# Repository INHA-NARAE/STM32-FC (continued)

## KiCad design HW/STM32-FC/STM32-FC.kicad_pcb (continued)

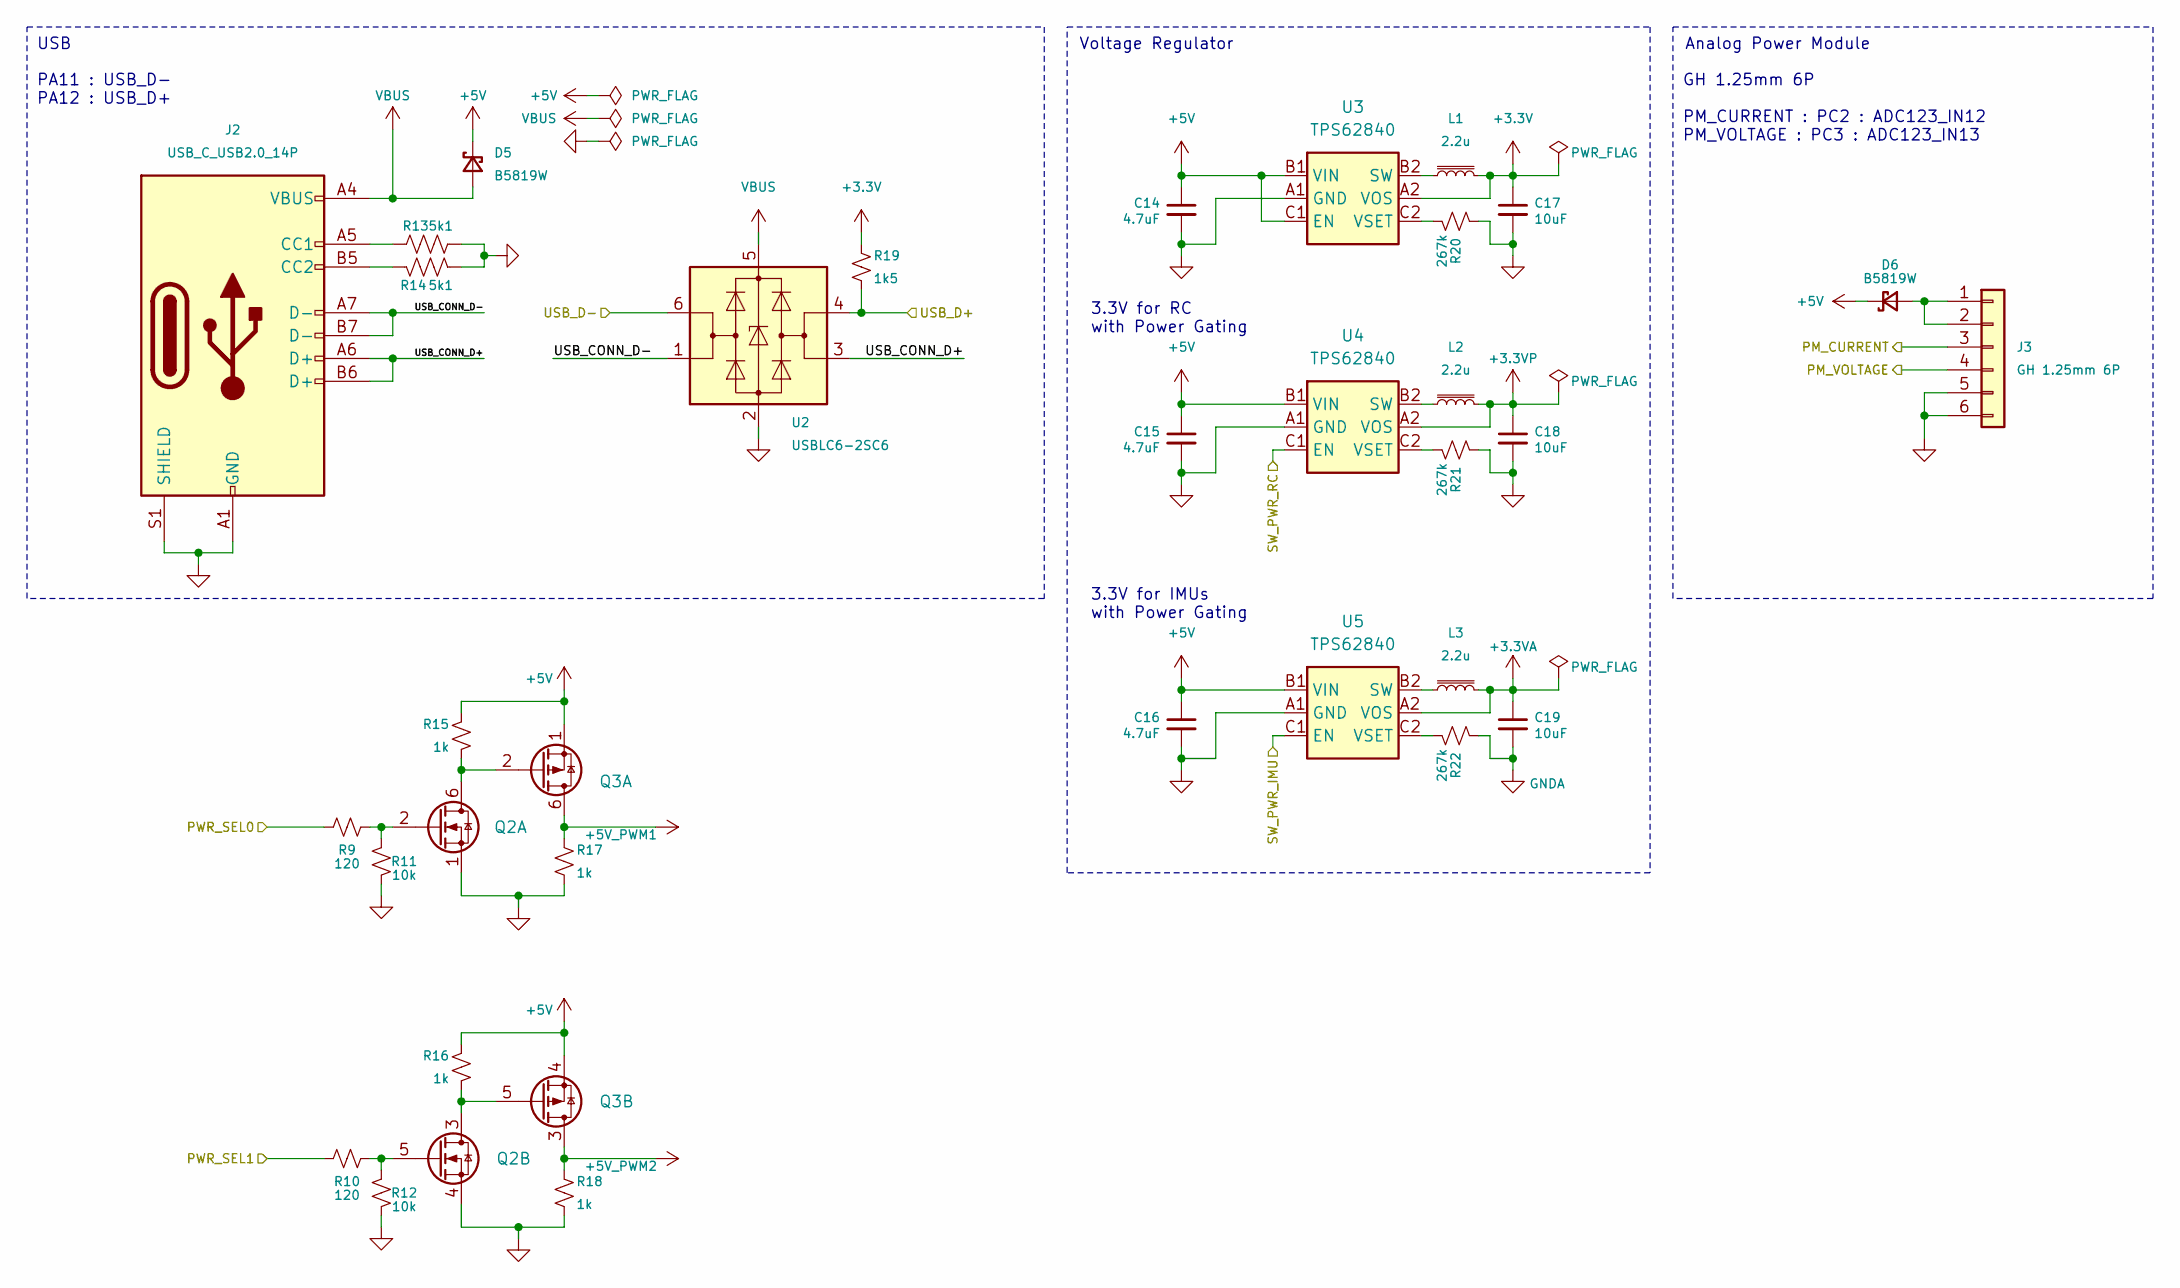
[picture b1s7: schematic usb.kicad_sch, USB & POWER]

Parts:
C14, C15, C16: 4.7uF; C_0402_1005Metric; LCSC C307423
C17, C18, C19: 10uF; C_0402_1005Metric; LCSC C307415
D5, D6: B5819W; D_SOD-323; LCSC C22624
J2: USB_C_USB2.0_14P; USB_C_Receptacle_GCT_USB4110; LCSC C709031
J3: GH 1.25mm 6P; JST_GH_SM06B-GHS-TB_06x1.25mm_Angled; LCSC C133065
L1, L2, L3: 2.2u; VLS201610ET-2R2M; LCSC C114768
Q2: PMDPB30XN; Nexperia_SOT1118; LCSC C478009
Q3: PMDPB55XP; Nexperia_SOT1118; LCSC C552752
R9, R10: 120; R_0402_1005Metric; LCSC C25079
R11, R12: 10k; R_0402_1005Metric; LCSC C25531
R13, R14: 5k1; R_0402_1005Metric; LCSC C25905
R15, R16, R17, R18: 1k; R_0402_1005Metric; LCSC C106235
R19: 1k5; R_0402_1005Metric; LCSC C25867
R20, R21, R22: 267k; R_0402_1005Metric; LCSC C2998050
U2: USBLC6-2SC6; SOT-23-6; LCSC C7519
U3, U4, U5: TPS62840; Texas_DSBGA-6_0.855x1.255mm_Layout2x3_P0.4mm_LevelC; LCSC C2071139

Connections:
+3.3V: C17.1, L1.2, R19.1, U3.A2 (VOS); also elsewhere on the board
+3.3VA: C19.1, L3.2, U5.A2 (VOS); also elsewhere on the board
+3.3VP: C18.1, L2.2, U4.A2 (VOS); also elsewhere on the board
+5V: C14.1, C15.1, C16.1, D5.1 (K), D6.1 (K), Q3.1 (S), Q3.4 (S), R15.1, R16.1, U3.B1 (VIN), U3.C1 (EN), U4.B1 (VIN), U5.B1 (VIN); also elsewhere on the board
+5V_PWM1: Q3.6 (D), Q3.7 (D), R17.1; also elsewhere on the board
+5V_PWM2: Q3.3 (D), Q3.8 (D), R18.1; also elsewhere on the board
/PM_CURRENT: J3.3; also elsewhere on the board
/PM_VOLTAGE: J3.4; also elsewhere on the board
/PWR_SEL0: R9.1; also elsewhere on the board
/PWR_SEL1: R10.1; also elsewhere on the board
/SW_PWR_IMU: U5.C1 (EN); also elsewhere on the board
/SW_PWR_RC: U4.C1 (EN); also elsewhere on the board
/USB & POWER/USB_CONN_D+: J2.A6 (D+), J2.B6 (D+), U2.3 (I/O2)
/USB & POWER/USB_CONN_D-: J2.A7 (D-), J2.B7 (D-), U2.1 (I/O1)
/USB_D+: R19.2, U2.4 (I/O2); also elsewhere on the board
/USB_D-: U2.6 (I/O1); also elsewhere on the board
unnamed: D6.2 (A), J3.1, J3.2
unnamed: J2.A5 (CC1), R13.1
unnamed: J2.B5 (CC2), R14.1
unnamed: Q2.2 (G), R9.2, R11.1
unnamed: Q2.5 (G), R10.2, R12.1
unnamed: Q2.6 (D), Q2.7 (D), Q3.2 (G), R15.2
unnamed: Q2.3 (D), Q2.8 (D), Q3.5 (G), R16.2
unnamed: L1.1, U3.B2 (SW)
unnamed: R20.2, U3.C2 (VSET)
unnamed: L2.1, U4.B2 (SW)
unnamed: R21.2, U4.C2 (VSET)
unnamed: L3.1, U5.B2 (SW)
unnamed: R22.2, U5.C2 (VSET)
VBUS: D5.2 (A), J2.A4 (VBUS), J2.A9 (VBUS), J2.B4 (VBUS), J2.B9 (VBUS), U2.5 (VBUS)

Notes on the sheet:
Analog Power Module
GH 1.25mm 6P PM_CURRENT : PC2 : ADC123_IN12 PM_VOLTAGE : PC3 : ADC123_IN13
Voltage Regulator
3.3V for IMUs with Power Gating
USB
3.3V for RC with Power Gating
PA11 : USB_D- PA12 : USB_D+

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
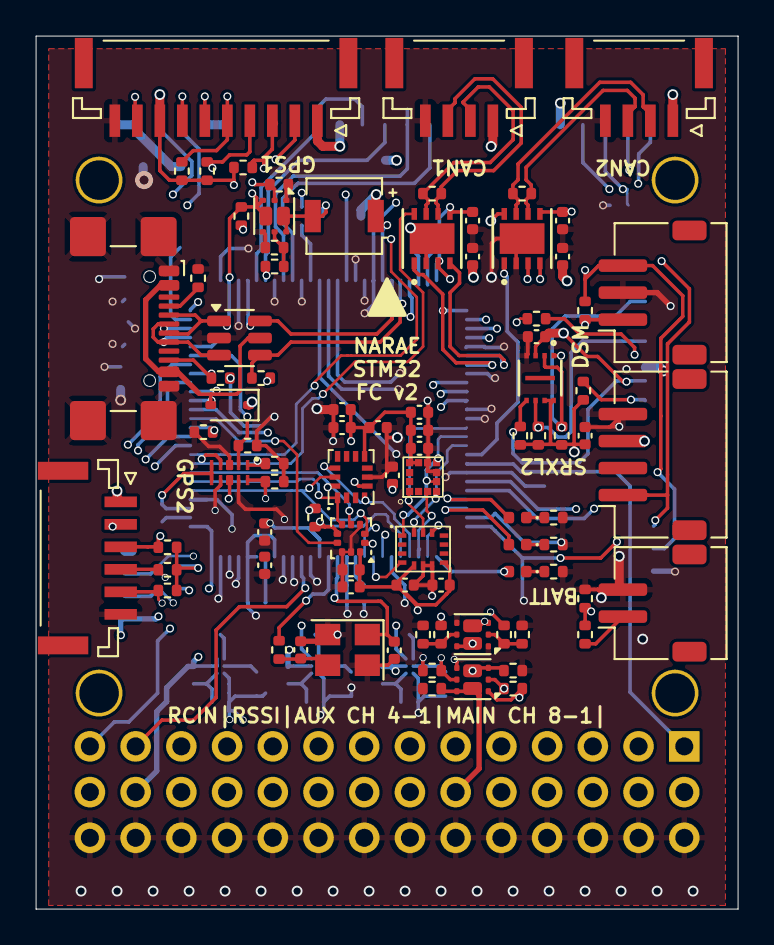
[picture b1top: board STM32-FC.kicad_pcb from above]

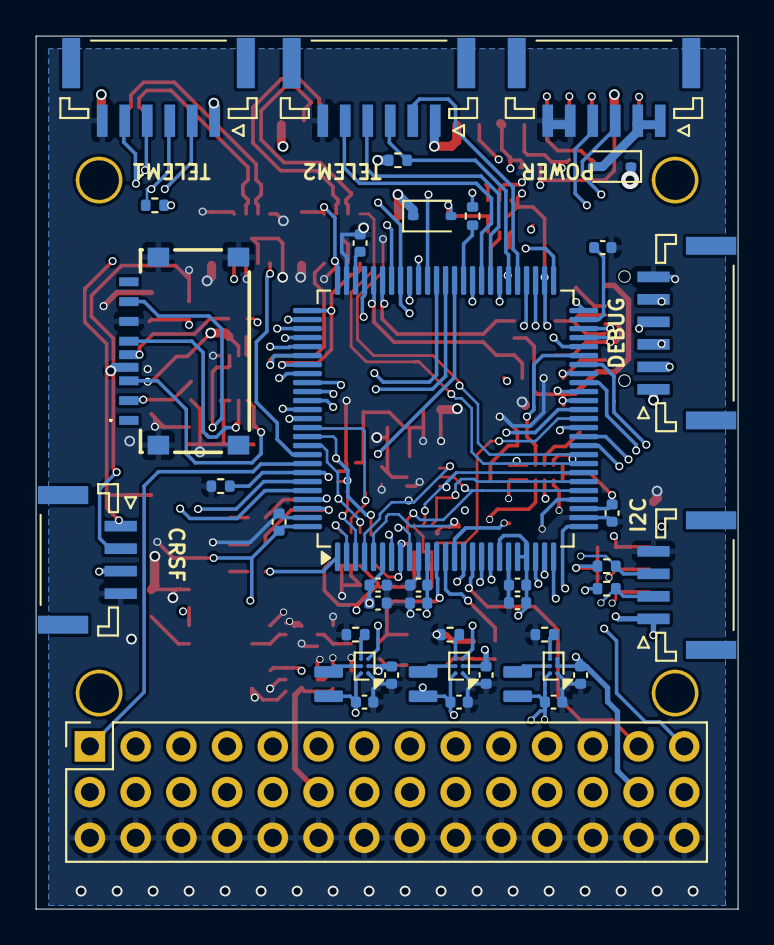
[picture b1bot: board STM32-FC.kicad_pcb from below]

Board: 4 copper layers, 39.0 x 48.5 mm, 133 parts (42 on the bottom side), 125 nets.

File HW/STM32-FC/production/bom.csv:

Designator,Footprint,Quantity,Value,LCSC Part #
BZ1,FUET-4020,1,FUET-4020,C391027
"C1, C4",0402,2,10pF,C1545
"C10, C11, C13, C20, C21, C22, C24, C29, C3, C30, C32, C33, C34, C35, C5, C8, C9",0402,17,100nF,C1525
C12,0402,1,1uF,C14445
"C14, C15, C16, C27",0402,4,4.7uF,C307423
"C17, C18, C19, C2, C28",0402,5,10uF,C307415
C23,0402,1,100pF,C152819
C25,0402,1,2.2nF,C84703
C26,0402,1,10nF,C15195
C31,0402,1,220nF,C16651
"C6, C7",0402,2,2.2uF,C170151
"D1, D5, D6",D_SOD-323,3,B5819W,C22624
D2,0402,1,Red,C130719
D3,0402,1,Yellow,C130721
D4,0402,1,Green,C130722
"J1, J10, J11, J12, J3",JST_GH_SM06B-GHS-TB_06x1.25mm_Angled,5,GH 1.25mm 6P,C133065
"J13, J14, J15, J16",JST_GH_SM04B-GHS-TB_04x1.25mm_Angled,4,GH 1.25mm 4P,C189895
J2,USB_C_Receptacle_GCT_USB4110,1,USB_C_USB2.0_14P,C709031
J4,TF06A,1,TF-06A,C693844
J5,JST_ZH_S2B-ZR-SM4A-TF_1x02-1MP_P1.50mm_Horizontal,1,JST ZH 1.5mm 2P,C265329
J6,PWM_Conn_3x14,1,PWM_Conn_3x14,C3327492
J7,JST_ZH_S4B-ZR-SM4A-TF_1x04-1MP_P1.50mm_Horizontal,1,ZH 1.5mm 4P,C485354
J8,JST_ZH_S3B-ZR-SM4A-TF_1x03-1MP_P1.50mm_Horizontal,1,ZH 1.5mm 3P,C72591
J9,JST_GH_SM10B-GHS-TB_10x1.25mm_Angled,1,GH 1.25mm 10P,C2683602 
"L1, L2, L3",VLS201610ET-2R2M,3,2.2u,C114768
"Q1, Q2",Nexperia_SOT1118,2,PMDPB30XN,C478009
Q3,Nexperia_SOT1118,1,PMDPB55XP,C552752
"R1, R11, R12, R2, R23, R24, R25, R26, R27, R28, R31, R32, R34, R36, R37, R38, R39, R40, R41, R42, R43, R44, R45, R46, R47, R5",0402,26,10k,C25531
"R10, R3, R33, R4, R48, R49, R6, R7, R8, R9",0402,10,120, C25079
"R13, R14",0402,2,5k1,C25905
"R15, R16, R17, R18, R30, R35",0402,6,1k,C106235
R19,0402,1,1k5,C25867
"R20, R21, R22",0402,3,267k,C2998050
R29,0402,1,15k,C25539
U1,LQFP-100_14x14mm_P0.5mm,1,STM32F407VETx,C28730
U10,ST_HLGA-10_2x2mm_P0.5mm_LayoutBorder3x2y,1,LPS22HH,C2827824
U11,TMUX1104,1,TMUX1104,C2865387
"U12, U13",VDFN8_3X3_MCH-L,2,ATA6561-GBQW,C617297
U2,SOT-23-6,1,USBLC6-2SC6,C7519
"U3, U4, U5",Texas_DSBGA-6_0.855x1.255mm_Layout2x3_P0.4mm_LevelC,3,TPS62840,C2071139
U6,USON_LUXIG TR_WIN-L,1,W25X40CLUXIG,C401661
U7,BMI323_L,1,BMI323,C5368700
U8,IIM42352_L,1,ICM-42688-P,C1850418
U9,LIS2MDLTR,1,LIS2MDLTR,C919695
Y1,Crystal_SMD_Abracon_ABM8G-4Pin_3.2x2.5mm,1,16MHz,C1985423

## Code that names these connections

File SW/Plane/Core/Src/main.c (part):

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		  FS_mannualMode();
	  }
	  else{
		  LL_GPIO_ResetOutputPin(LED_RED_GPIO_Port, LED_RED_Pin);
		  SERVO_control();
	  }

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
  LL_AHB1_GRP1_EnableClock(LL_AHB1_GRP1_PERIPH_GPIOC);
  /**ADC1 GPIO Configuration
  PC1   ------> ADC1_IN11
  */
  GPIO_InitStruct.Pin = RSSI_Pin;
  GPIO_InitStruct.Mode = LL_GPIO_MODE_ANALOG;
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
  LL_AHB1_GRP1_EnableClock(LL_AHB1_GRP1_PERIPH_GPIOA);
  /**SPI1 GPIO Configuration
  PA5   ------> SPI1_SCK
  PA6   ------> SPI1_MISO
  PA7   ------> SPI1_MOSI
  */
  GPIO_InitStruct.Pin = LL_GPIO_PIN_5|LL_GPIO_PIN_6|LL_GPIO_PIN_7;
  GPIO_InitStruct.Mode = LL_GPIO_MODE_ALTERNATE;
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  /* USER CODE END TIM1_Init 2 */
  LL_AHB1_GRP1_EnableClock(LL_AHB1_GRP1_PERIPH_GPIOE);
  /**TIM1 GPIO Configuration
  PE11   ------> TIM1_CH2
  PE13   ------> TIM1_CH3
  */
  GPIO_InitStruct.Pin = MAIN_CH11_Pin|MAIN_CH12_Pin;
  GPIO_InitStruct.Mode = LL_GPIO_MODE_ALTERNATE;
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  LL_AHB1_GRP1_EnableClock(LL_AHB1_GRP1_PERIPH_GPIOB);
  LL_AHB1_GRP1_EnableClock(LL_AHB1_GRP1_PERIPH_GPIOC);
  /**TIM3 GPIO Configuration
  PB0   ------> TIM3_CH3
  PB1   ------> TIM3_CH4
  PC6   ------> TIM3_CH1
  PC7   ------> TIM3_CH2
  */
  GPIO_InitStruct.Pin = MAIN_CH9_Pin|MAIN_CH10_Pin;
  GPIO_InitStruct.Mode = LL_GPIO_MODE_ALTERNATE;
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  LL_AHB1_GRP1_EnableClock(LL_AHB1_GRP1_PERIPH_GPIOD);
  LL_AHB1_GRP1_EnableClock(LL_AHB1_GRP1_PERIPH_GPIOB);
  /**TIM4 GPIO Configuration
  PD14   ------> TIM4_CH3
  PD15   ------> TIM4_CH4
  PB7   ------> TIM4_CH2
  */
  GPIO_InitStruct.Pin = Buzzer_Pin|MAIN_CH4_Pin;
  GPIO_InitStruct.Mode = LL_GPIO_MODE_ALTERNATE;
  GPIO_InitStruct.Speed = LL_GPIO_SPEED_FREQ_LOW;
  GPIO_InitStruct.OutputType = LL_GPIO_OUTPUT_PUSHPULL;
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  /* USER CODE END TIM5_Init 2 */
  LL_AHB1_GRP1_EnableClock(LL_AHB1_GRP1_PERIPH_GPIOA);
  /**TIM5 GPIO Configuration
  PA0-WKUP   ------> TIM5_CH1
  PA1   ------> TIM5_CH2
  PA2   ------> TIM5_CH3
  PA3   ------> TIM5_CH4
  */
  GPIO_InitStruct.Pin = MAIN_CH5_Pin|MAIN_CH6_Pin|MAIN_CH7_Pin|MAIN_CH8_Pin;
  GPIO_InitStruct.Mode = LL_GPIO_MODE_ALTERNATE;
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
  LL_AHB1_GRP1_EnableClock(LL_AHB1_GRP1_PERIPH_GPIOC);
  /**UART4 GPIO Configuration
  PC10   ------> UART4_TX
  PC11   ------> UART4_RX
  */
  GPIO_InitStruct.Pin = GPS1_TX_Pin|GPS2_RX_Pin;
  GPIO_InitStruct.Mode = LL_GPIO_MODE_ALTERNATE;
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  LL_AHB1_GRP1_EnableClock(LL_AHB1_GRP1_PERIPH_GPIOC);
  LL_AHB1_GRP1_EnableClock(LL_AHB1_GRP1_PERIPH_GPIOD);
  /**UART5 GPIO Configuration
  PC12   ------> UART5_TX
  PD2   ------> UART5_RX
  */
  GPIO_InitStruct.Pin = GPS2_TX_Pin;
  GPIO_InitStruct.Mode = LL_GPIO_MODE_ALTERNATE;
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
  LL_AHB1_GRP1_EnableClock(LL_AHB1_GRP1_PERIPH_GPIOA);
  /**USART1 GPIO Configuration
  PA9   ------> USART1_TX
  */
  GPIO_InitStruct.Pin = RC_SRXL2_Pin;
  GPIO_InitStruct.Mode = LL_GPIO_MODE_ALTERNATE;
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
  LL_AHB1_GRP1_EnableClock(LL_AHB1_GRP1_PERIPH_GPIOD);
  /**USART2 GPIO Configuration
  PD3   ------> USART2_CTS
  PD4   ------> USART2_RTS
  PD5   ------> USART2_TX
  PD6   ------> USART2_RX
  */
  GPIO_InitStruct.Pin = LL_GPIO_PIN_3|LL_GPIO_PIN_4|Telm1_TX_Pin|Telm1_RX_Pin;
  GPIO_InitStruct.Mode = LL_GPIO_MODE_ALTERNATE;
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
  LL_AHB1_GRP1_EnableClock(LL_AHB1_GRP1_PERIPH_GPIOD);
  /**USART3 GPIO Configuration
  PD8   ------> USART3_TX
  PD9   ------> USART3_RX
  PD11   ------> USART3_CTS
  PD12   ------> USART3_RTS
  */
  GPIO_InitStruct.Pin = Telm2_TX_Pin|Telm2_RX_Pin|LL_GPIO_PIN_11|LL_GPIO_PIN_12;
  GPIO_InitStruct.Mode = LL_GPIO_MODE_ALTERNATE;
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  LL_AHB1_GRP1_EnableClock(LL_AHB1_GRP1_PERIPH_GPIOD);

  /**/
  LL_GPIO_ResetOutputPin(GPIOE, LED_BLUE_Pin|GYRO1_NSS_Pin|BARO_NSS_Pin|LED_RED_Pin
                          |LED_YELLOW_Pin);

  /**/
  LL_GPIO_ResetOutputPin(GPS1_SW_LED_GPIO_Port, GPS1_SW_LED_Pin);

  /**/
  GPIO_InitStruct.Pin = LED_BLUE_Pin|GYRO1_NSS_Pin|BARO_NSS_Pin|LED_RED_Pin
                          |LED_YELLOW_Pin;
  GPIO_InitStruct.Mode = LL_GPIO_MODE_OUTPUT;
  GPIO_InitStruct.Speed = LL_GPIO_SPEED_FREQ_LOW;
  GPIO_InitStruct.OutputType = LL_GPIO_OUTPUT_PUSHPULL;
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  LL_GPIO_Init(GPIOE, &GPIO_InitStruct);

  /**/
  GPIO_InitStruct.Pin = BARO_INT_Pin;
  GPIO_InitStruct.Mode = LL_GPIO_MODE_INPUT;
  GPIO_InitStruct.Pull = LL_GPIO_PULL_NO;
  LL_GPIO_Init(BARO_INT_GPIO_Port, &GPIO_InitStruct);

  /**/
  GPIO_InitStruct.Pin = GPS1_SW_LED_Pin;
  GPIO_InitStruct.Mode = LL_GPIO_MODE_OUTPUT;
  GPIO_InitStruct.Speed = LL_GPIO_SPEED_FREQ_LOW;
  GPIO_InitStruct.OutputType = LL_GPIO_OUTPUT_PUSHPULL;
  GPIO_InitStruct.Pull = LL_GPIO_PULL_NO;
  LL_GPIO_Init(GPS1_SW_LED_GPIO_Port, &GPIO_InitStruct);

  /**/
  LL_SYSCFG_SetEXTISource(LL_SYSCFG_EXTI_PORTE, LL_SYSCFG_EXTI_LINE14);
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
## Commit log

2025-06-19 LPS22HH Circuit update
2025-06-19 HW Lib and RC code refactoring, GCS_log united and BMI323 IMU init.
2025-06-19 improve to save RC Channel data in msg of RC_channel.
